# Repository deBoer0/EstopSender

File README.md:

# EstopSender
Estop button with 433mhz sender on single contact

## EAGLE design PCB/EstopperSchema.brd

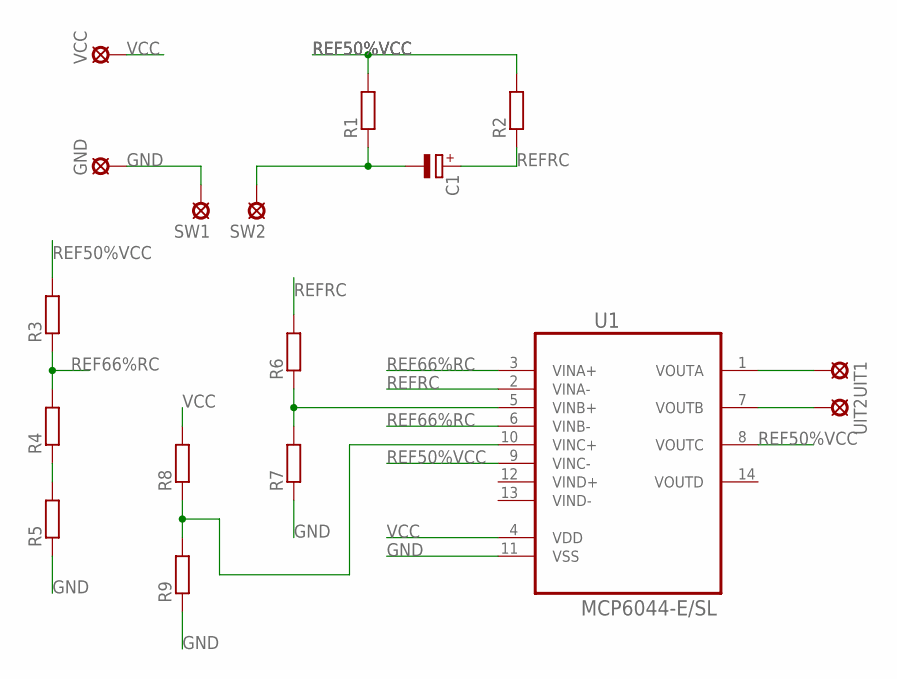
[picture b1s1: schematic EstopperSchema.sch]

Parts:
C1: CPOL-EU140CLH-0810; 140CLH-0810
GND: LSP11
R1, R2, R3, R4, R5, R6, R7, R8, R9: R-EU_M1206; M1206
SW1, SW2: LSP11
U1: MCP6044-E/SL; SOIC127P600X175-14N
UIT1, UIT2: LSP11
VCC: LSP11

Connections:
GND: GND.MP, R5.1, R7.1, R9.1, SW1.MP, U1.11 (VSS)
unnamed: R6.1, R7.2, U1.5 (VINB+)
unnamed: C1.-, R1.1, SW2.MP
unnamed: R4.1, R5.2
unnamed: U1.1 (VOUTA), UIT1.MP
unnamed: U1.7 (VOUTB), UIT2.MP
unnamed: R8.1, R9.2, U1.10 (VINC+)
REF50%VCC: R1.2, R2.2, R3.2, U1.8 (VOUTC), U1.9 (VINC-)
REF66%RC: R3.1, R4.2, U1.3 (VINA+), U1.6 (VINB-)
REFRC: C1.+, R2.1, R6.2, U1.2 (VINA-)
VCC: R8.2, U1.4 (VDD), VCC.MP

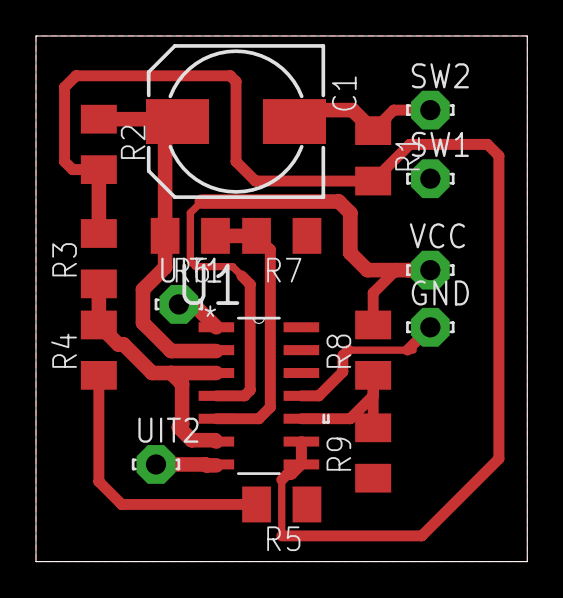
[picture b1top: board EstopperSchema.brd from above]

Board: 2 copper layers, 27.3 x 29.2 mm, 17 parts (0 on the bottom side), 11 nets.

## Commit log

2024-11-20 Initial commit
    Initial Drawings added
